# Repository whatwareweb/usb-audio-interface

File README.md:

# usb-audio-interface
USB audio interface based on PCM2906C IC

**NOTE: This design is tested to work properly. If you have any problems using this design, feel free to send me an email or leave a GitHub issue.**

## description
This USB audio interface board has standard RCA inputs and outputs for both analog and digital signals. I designed it because the only products that exist that can record digital S/PDIF over coaxial cost >$200 USD.

While it was designed primarily for digital audio capture and output, I also put thought into the analog design. It has high-capacitance, low ESR output capacitors for good low-frequency response, and an optimized layout for decoupling capacitors and crystal circuitry, to improve ADC/DAC performance, and to reduce jitter, respectively, while maintaining a super compact form factor of only 4x5cm. It could have been even more compact, but at the expense of removing industry standard RCA jacks.

## assembly
The BOM in the KiCAD project is up to date and contains no out-of-production parts at time of creation. All parts were ordered from Mouser Electronics. This was designed to be hand solderable, with SMD components including larger pads in the footprint, however as it does use 0603 components, reflow soldering is preferable if possible.

## features
 - USB-C port with reversibility support
 - Low ESR high capacitance output and input capacitors for good low-frequency response
 - Analog and digital inputs and outputs
 - Compact design layout
 - Standard RCA jacks

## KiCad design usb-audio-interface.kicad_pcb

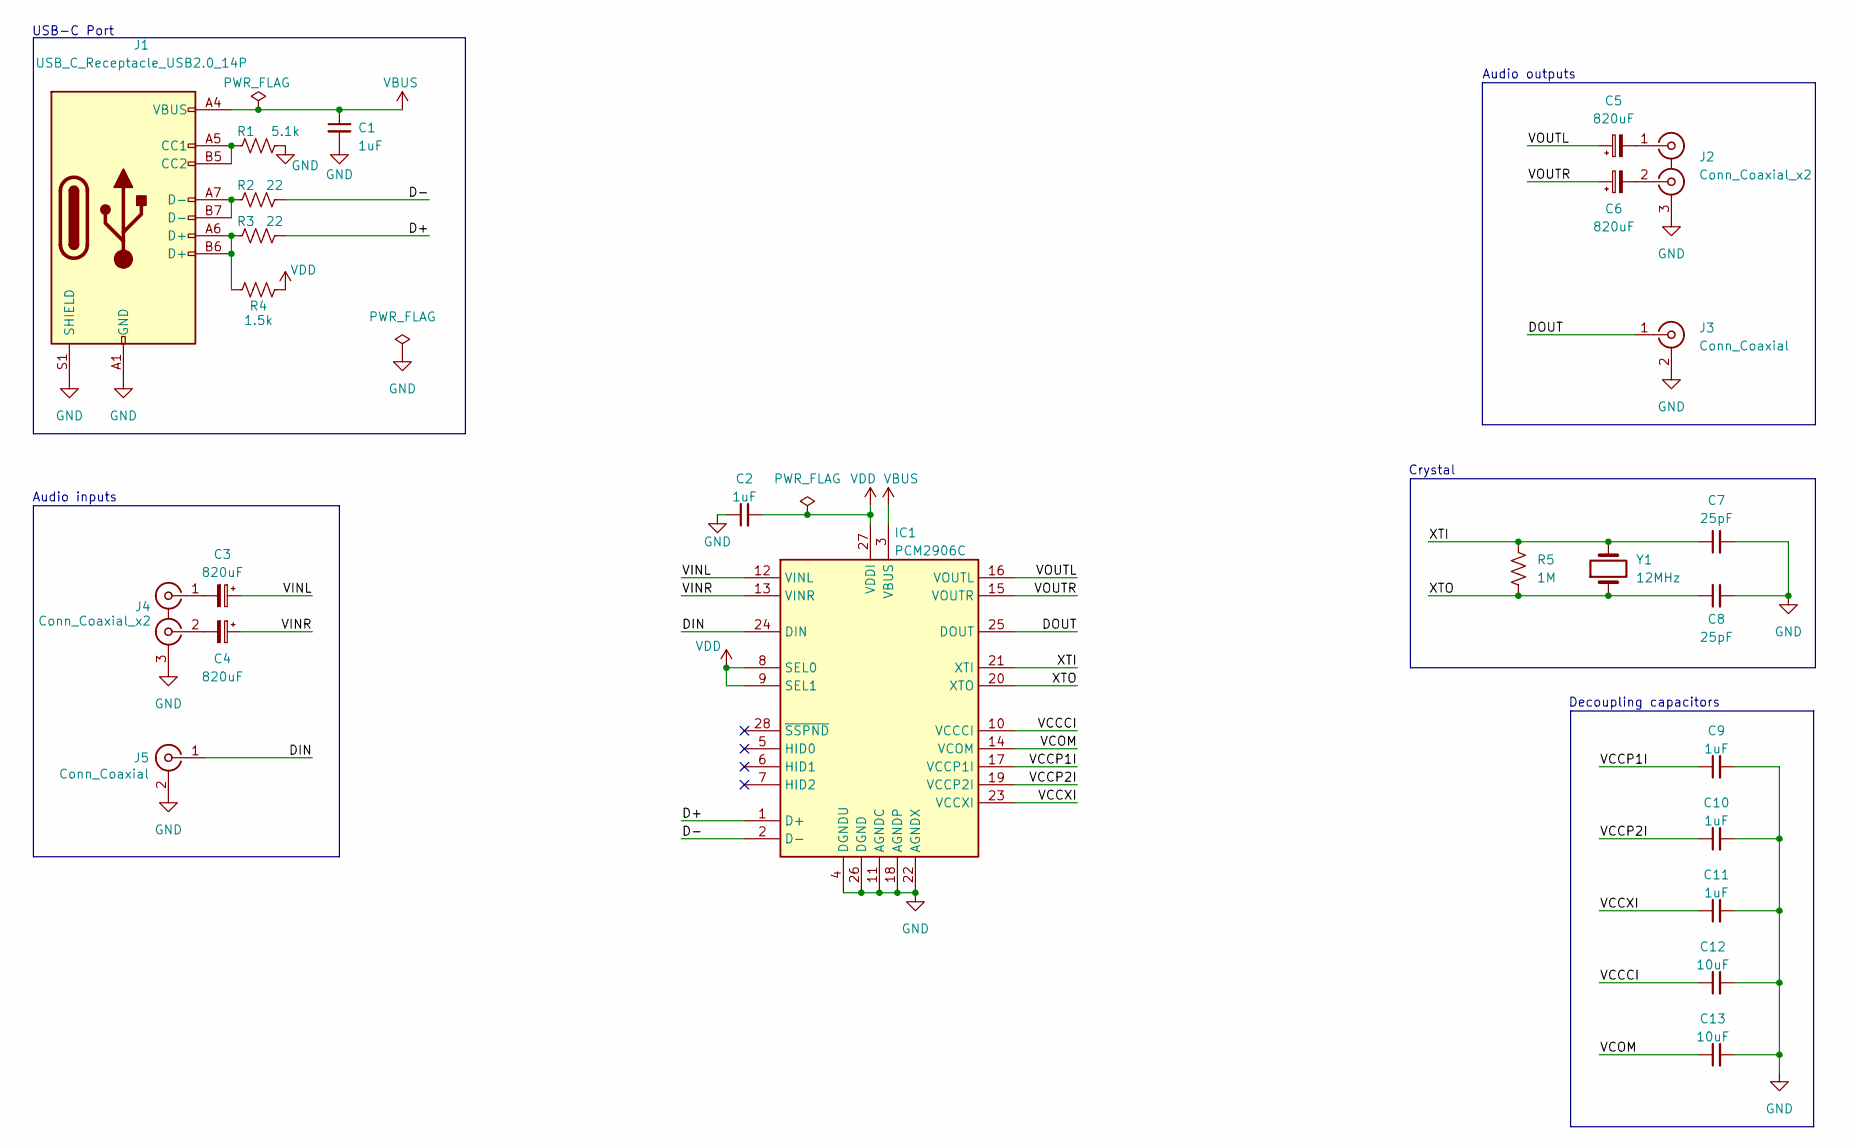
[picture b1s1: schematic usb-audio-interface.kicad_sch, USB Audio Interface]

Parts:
C1: 1uF; C_0603_1608Metric_Pad1.08x0.95mm_HandSolder; Mfr. # FG28X7R1E105KRT00
C2, C9, C10, C11: 1uF; C_0603_1608Metric_Pad1.08x0.95mm_HandSolder; Manufacturer_Part_Number CL10A105KQ8NNNC
C3, C4, C5, C6: 820uF; CP_Radial_D8.0mm_P3.50mm; Manufacturer_Part_Number 6.3ZLH820MEFC8X11.5
C7, C8: 25pF; C_0603_1608Metric_Pad1.08x0.95mm_HandSolder; Manufacturer_Part_Number CC0603JRNPO9BN250
C12, C13: 10uF; C_0805_2012Metric_Pad1.18x1.45mm_HandSolder; Manufacturer_Part_Number CL21A106KOQNNNG
IC1: PCM2906C; SSOP-28_5.3x10.2mm_P0.65mm; Mouser Part Number 595-PCM2906CDBR
J1: USB_C_Receptacle_USB2.0_14P; USB_C_Receptacle_GCT_USB4105-xx-A_16P_TopMnt_Horizontal; Mfr. # USB4105
J2, J4: Conn_Coaxial_x2; PJRAN2X1U01AUX; Manufacturer_Part_Number PJRAN2X1U01AUX
J3, J5: Conn_Coaxial; 1560099E; Manufacturer_Part_Number 156-0099-E
R1: 5.1k; R_0603_1608Metric_Pad0.98x0.95mm_HandSolder; Mfr. # CF18JT5K10
R2, R3: 22; R_0603_1608Metric_Pad0.98x0.95mm_HandSolder; Mfr. # CFR-12JB-52-30R
R4: 1.5k; R_0603_1608Metric_Pad0.98x0.95mm_HandSolder; Manufacturer_Part_Number CRGCQ0603F1K5
R5: 1M; R_0603_1608Metric_Pad0.98x0.95mm_HandSolder; Manufacturer_Part_Number RK73B1JTTDD105J
Y1: 12MHz; Crystal_SMD_HC49-SD; Manufacturer_Part_Number ABLS-12.000MHz-B4H-T

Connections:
/D+: IC1.1 (D+), R3.2
/D-: IC1.2 (D-), R2.2
/DIN: IC1.24 (DIN), J5.1 (In)
/DOUT: IC1.25 (DOUT), J3.1 (In)
/VCCCI: C12.1, IC1.10 (VCCCI)
/VCCP1I: C9.1, IC1.17 (VCCP1I)
/VCCP2I: C10.1, IC1.19 (VCCP2I)
/VCCXI: C11.1, IC1.23 (VCCXI)
/VCOM: C13.1, IC1.14 (VCOM)
/VINL: C3.1, IC1.12 (VINL)
/VINR: C4.1, IC1.13 (VINR)
/VOUTL: C5.1, IC1.16 (VOUTL)
/VOUTR: C6.1, IC1.15 (VOUTR)
/XTI: C7.1, IC1.21 (XTI), R5.1, Y1.2
/XTO: C8.1, IC1.20 (XTO), R5.2, Y1.1
GND: C1.2, C2.1, C7.2, C8.2, C9.2, C10.2, C11.2, C12.2, C13.2, IC1.4 (DGNDU), IC1.11 (AGNDC), IC1.18 (AGNDP), IC1.22 (AGNDX), IC1.26 (DGND), J1.A1 (GND), J1.A12 (GND), J1.B1 (GND), J1.B12 (GND), J1.S1 (SHIELD), J2.3 (EXT), J3.2 (Ext), J4.3 (EXT), J5.2 (Ext), R1.2
unnamed: J1.A5 (CC1), J1.B5 (CC2), R1.1
unnamed: J1.A6 (D+), J1.B6 (D+), R3.1, R4.1
unnamed: J1.A7 (D-), J1.B7 (D-), R2.1
unnamed: C5.2, J2.1 (IN1)
unnamed: C6.2, J2.2 (IN2)
unnamed: C3.2, J4.1 (IN1)
unnamed: C4.2, J4.2 (IN2)
VBUS: C1.1, IC1.3 (VBUS), J1.A4 (VBUS), J1.A9 (VBUS), J1.B4 (VBUS), J1.B9 (VBUS)
VDD: C2.2, IC1.8 (SEL0), IC1.9 (SEL1), IC1.27 (VDDI), R4.2

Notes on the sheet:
Audio outputs
Crystal
USB-C Port
Audio inputs
Decoupling capacitors

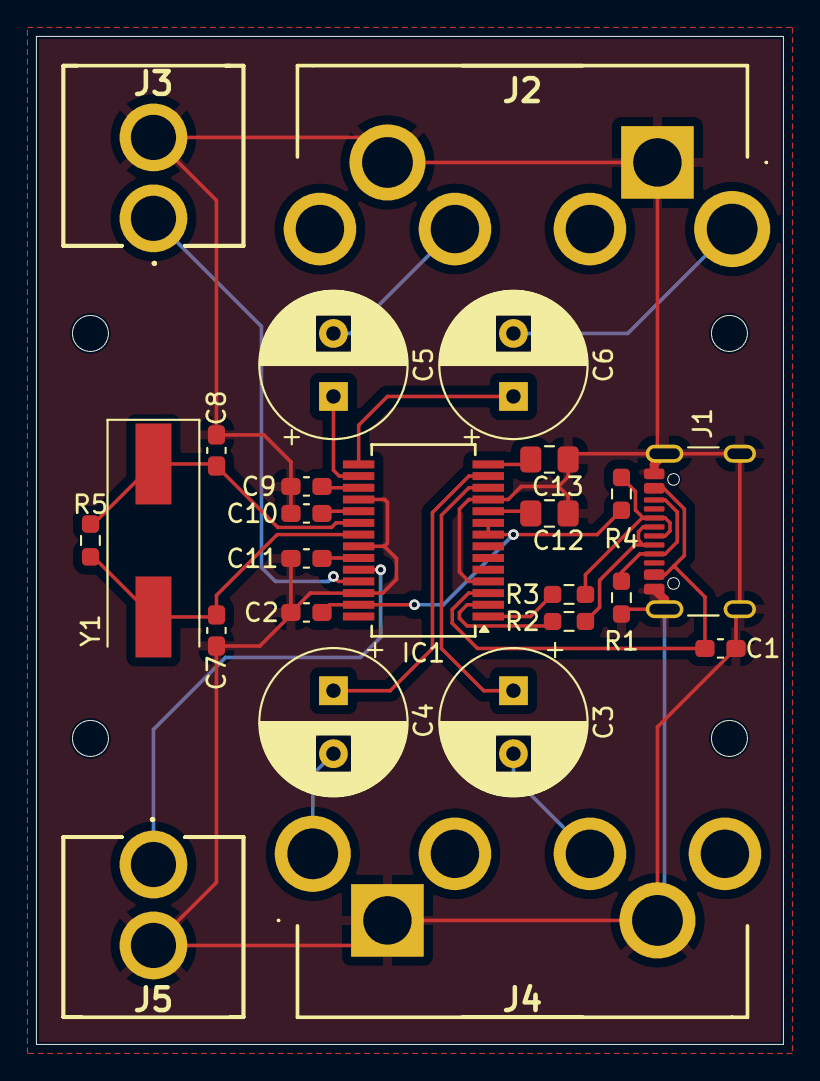
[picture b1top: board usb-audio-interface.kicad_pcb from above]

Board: 2 copper layers, 41.5 x 56.0 mm, 25 parts (0 on the bottom side), 25 nets.

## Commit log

2025-01-08 Create LICENSE
2025-01-27 Initial schematic
2025-01-27 Update schematic and start on footprints
2025-01-28 finish schematic
2025-01-28 update pcb
2025-01-29 finish pcb
2025-02-01 update schematic
2025-02-10 track width for crystal
2025-02-10 finish board
2025-02-10 update bom
2025-02-10 add mounting holes
